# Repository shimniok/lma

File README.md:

lma
===
Lost Model Alarm for finding your lost aircraft.

[User Guide](https://github.com/shimniok/lma/blob/master/firmware/UserGuide.md)

Ultra Micro park flyer planes like the Hobbyzone Champ or Parkzone UM Corsair are light (~40g) and could be blown downwind and out of sight. That's what happened to my Champ.

LMA's on the market usually have 3-pin servo connectors but these RTF planes don't have a place to plug them.

So I decided to make an ultra-light, standalone LMA. Here it is in its various versions along with firmware.

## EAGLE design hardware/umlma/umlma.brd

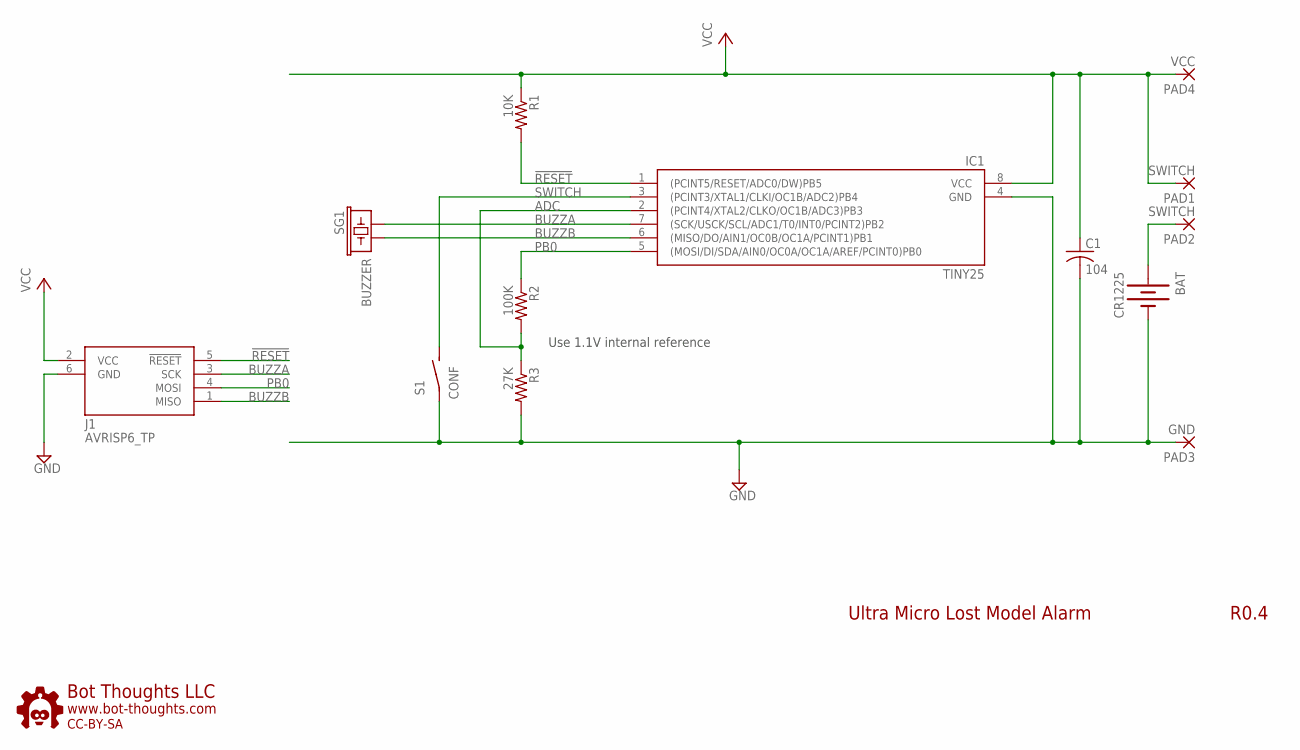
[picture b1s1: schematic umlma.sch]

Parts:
BAT: CR1225; BATTCON_12MM_PTH
C1: 104; C0603K; PARTNO GRM188R60J105KA01D
IC1: TINY25; SOIC8N
J1: AVRISP6_TP; 2X3_TP
PAD1, PAD2: SWITCH; 1,6/0,8
PAD3: GND; 1,6/0,8
PAD4: VCC; 1,6/0,8
R1: 10K; R0603; PARTNO ERJ-3GEYJ102V
R2: 100K; R0603; PARTNO ERJ-3GEYJ102V
R3: 27K; R0603; PARTNO ERJ-3GEYJ102V
S1: CONF; 3X4X2TACT
SG1: BUZZER; BUZZER_14MM_V_PTH; PARTNO AT-1438-TWT-R
U$1: BTLOGO-LOGO-SM; BTLOGOS

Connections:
!RESET: IC1.1 ((PCINT5/RESET/ADC0/DW)PB5), J1.5 (!RESET), R1.2
ADC: IC1.2 ((PCINT4/XTAL2/CLKO/OC1B/ADC3)PB3), R2.2, R3.1
BUZZA: IC1.7 ((SCK/USCK/SCL/ADC1/T0/INT0/PCINT2)PB2), J1.3 (SCK), SG1.P$5 (1)
BUZZB: IC1.6 ((MISO/DO/AIN1/OC0B/OC1A/PCINT1)PB1), J1.1 (MISO), SG1.P$6 (2)
GND: BAT.GND (-), C1.2, IC1.4 (GND), J1.6 (GND), PAD3.1, R3.2, S1.P$1
unnamed: BAT.VCC@1 (+), PAD2.1
PB0: IC1.5 ((MOSI/DI/SDA/AIN0/OC0A/OC1A/AREF/PCINT0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), J1.4 (MOSI), R2.1
SWITCH: IC1.3 ((PCINT3/XTAL1/CLKI/OC1B/ADC2)PB4), S1.P$2 (S)
VCC: C1.1, IC1.8 (VCC), J1.2 (VCC), PAD1.1, PAD4.1, R1.1

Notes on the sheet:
Ultra Micro Lost Model Alarm
R0.4
Use 1.1V internal reference

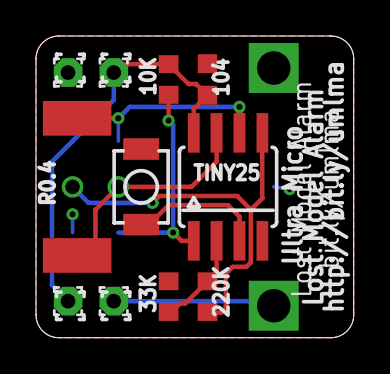
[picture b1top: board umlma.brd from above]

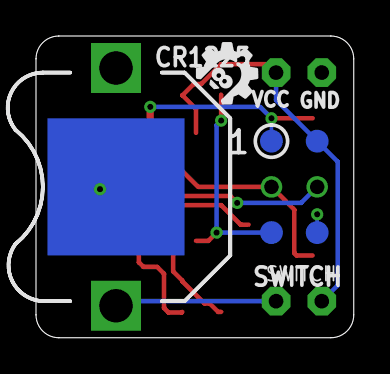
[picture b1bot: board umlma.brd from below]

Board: 2 copper layers, 17.7 x 16.8 mm, 14 parts (3 on the bottom side), 9 nets.

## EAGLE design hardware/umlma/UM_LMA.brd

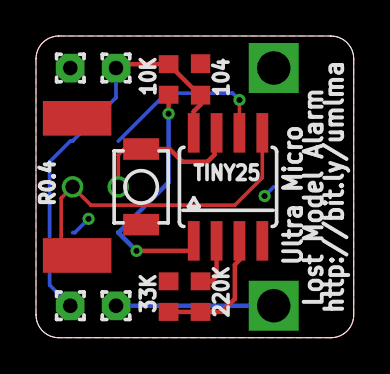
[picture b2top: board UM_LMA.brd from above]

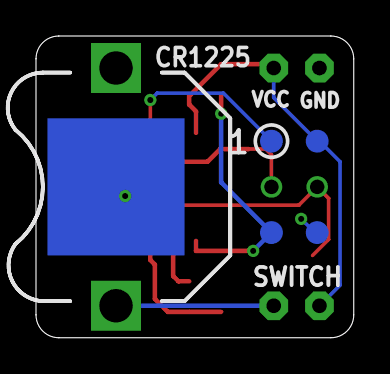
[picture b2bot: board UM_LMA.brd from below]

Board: 2 copper layers, 17.7 x 16.8 mm, 13 parts (2 on the bottom side), 9 nets.

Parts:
BAT: CR1225; BATTCON_12MM_PTH
C1: 104; C0603K
IC1: TINY25; SOIC8N
J1: AVRISP6_TP; 2X3_TP
PAD1, PAD2: SWITCH; 1,6/0,8
PAD3: GND; 1,6/0,8
PAD4: VCC; 1,6/0,8
R1: 10K; R0603
R2: 220K; R0603
R3: 33K; R0603
S1: CONF; 3X4X2TACT
SG1: BUZZER; BUZZER_14MM_V_PTH

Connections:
!RESET: IC1.1, J1.5, R1.2
GND: BAT.GND, C1.2, IC1.4, J1.6, PAD3.1, R3.2, S1.P$1, SG1.P$6
MISO: IC1.6, J1.1
MOSI: IC1.5, J1.4, SG1.P$5
unnamed: BAT.VCC@1, PAD2.1
unnamed: IC1.2, R2.1
SCK: IC1.7, J1.3, S1.P$2
VCC: C1.1, IC1.8, J1.2, PAD1.1, PAD4.1, R1.1
VTEST: IC1.3, R2.2, R3.1

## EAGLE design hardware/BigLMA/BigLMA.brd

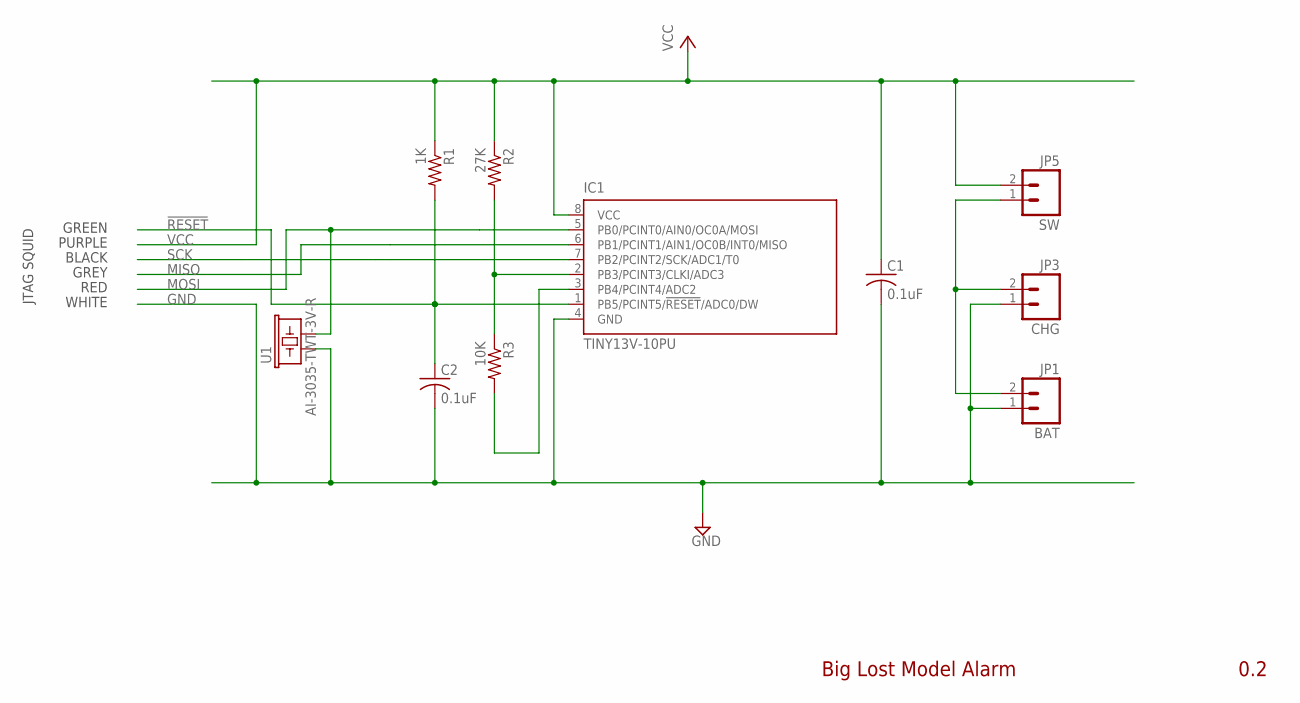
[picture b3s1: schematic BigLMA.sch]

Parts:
C1, C2: 0.1uF; C0603; PARTNO GRM188R60J105KA01D
IC1: TINY13V-10PU; DIL08; PARTNO ATTINY13V-10PU
JP1: BAT; JST-2-PTH
JP3: CHG; 1X02
JP5: SW; 1X02
R1: 1K; R0603; PARTNO ERJ-3GEYJ102V
R2: 27K; R0603; PARTNO RR0816P-273-D
R3: 10K; R0603; PARTNO RR0816P-103-D
U1: AI-3035-TWT-3V-R; BUZZER-30MM_PTH; PARTNO AI-3035-TWT-3V-R

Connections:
!RESET: C2.1, IC1.1 (PB5/PCINT5/!RESET!/ADC0/DW), R1.2
GND: C1.2, C2.2, IC1.4 (GND), JP1.1, JP3.1, U1.P$1 (1)
MISO: IC1.6 (PB1/PCINT1/AIN1/OC0B/INT0/MISO)
MOSI: IC1.5 (PB0/PCINT0/AIN0/OC0A/MOSI), U1.P$2 (2)
unnamed: IC1.2 (PB3/PCINT3/CLKI/ADC3), R2.2, R3.1
unnamed: JP1.2, JP3.2, JP5.1
unnamed: IC1.3 (PB4/PCINT4/ADC2), R3.2
SCK: IC1.7 (PB2/PCINT2/SCK/ADC1/T0)
VCC: C1.1, IC1.8 (VCC), JP5.2, R1.1, R2.1

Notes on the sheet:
WHITE
RED
GREY
BLACK
PURPLE
GREEN
JTAG SQUID
Big Lost Model Alarm
0.2

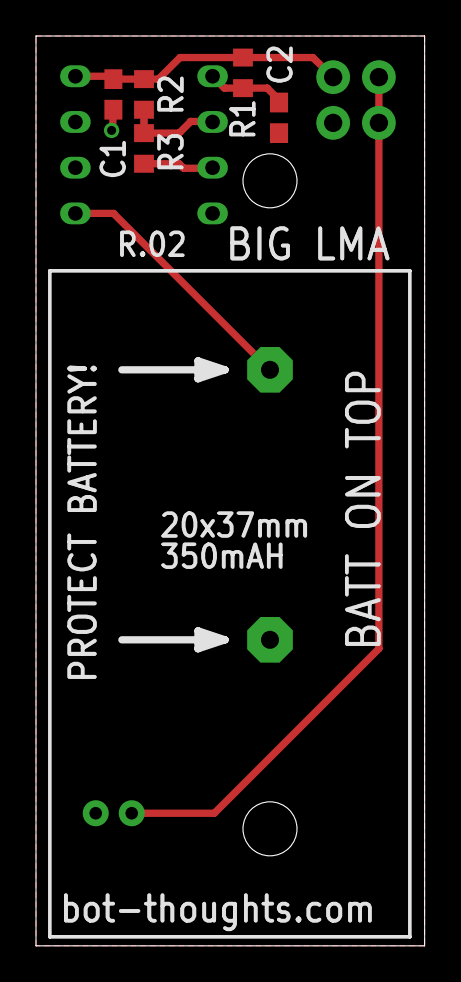
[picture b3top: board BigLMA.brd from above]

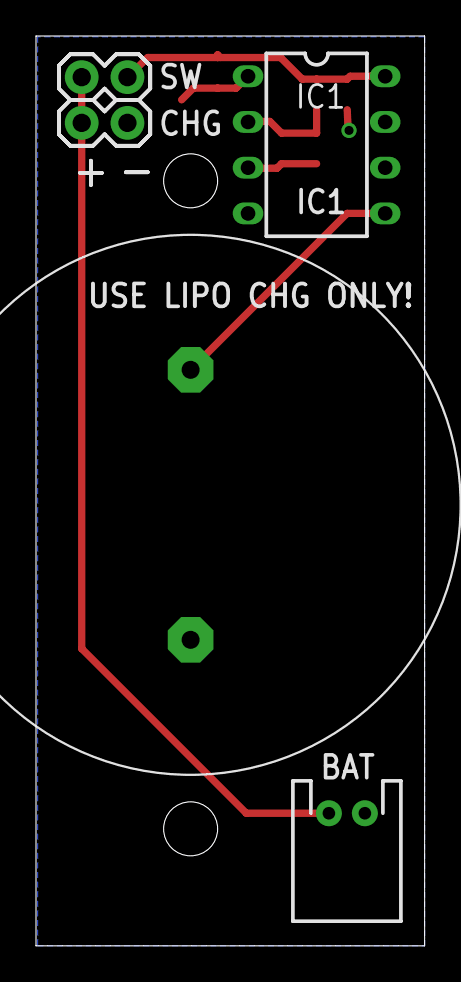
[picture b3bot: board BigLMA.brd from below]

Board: 2 copper layers, 21.6 x 50.5 mm, 11 parts (5 on the bottom side), 7 nets.

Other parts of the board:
U$1: LIPO_20X37

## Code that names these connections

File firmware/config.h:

#ifndef _CONFIG_H
#define _CONFIG_H

//#define DEBUG 1

#define BUZZA   PB1     // ATtiny25 Pin 6
#define BUZZB   PB2     // ATtiny25 Pin 7
#define SWITCH  PB4     // ATtiny25 Pin 3
#define LED     PB0     // ATtiny25 Pin 5
#define ADC     PB3     // ATtiny25 Pin 2
#define ADC_EN  PB0     // ATtiny25 Pin 5

#define WARN_PERIOD      10   // Delay period between signal (seconds) -- initial period
#define WARN_PERIOD_LOW  60   // If battery voltage is low, use longer period between beeps
#define BATT_PERIOD     600   // Time in seconds between checking battery voltage

#endif

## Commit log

2014-09-11 converting to git
2014-09-11 Renamed LMA to UMLMA
2014-12-02 added silk file
2014-12-02 Fixing AVRStudio4 build, added dep directory under default
2014-12-02 adding AVRstudio makefile
2014-12-02 added gitignore
2014-12-02 minor mods to src and Makefile
2014-12-02 added adc files from big lma
2014-12-02 added config.h
2014-12-02 Added voltage call / beep
2014-12-03 Modified adc.c to convert based on 3V coin battery and umlma voltage divider (220k/100k)
2014-12-03 Modified code to simply check if volts < 2.6V and warn otherwise beep ok
2014-12-03 converted initADC() to macro to reduce size
2014-12-03 added morse module and converted small once-used functions to macros
2014-12-03 added buzzer module, redefined beepOn() and beepOff() as functions to save space
2014-12-04 Added battery low voltage warning on startup with auto-calibration
2014-12-04 renamed adc.* to battery.*, renamed UM_LMA.c to lma.c
2014-12-04 Renamed project from UM_LMA to lma, modified various output files in the avr studio files
2014-12-04 added ADC shutdown for t13a
2014-12-04 Added user guide
2014-12-04 Added more documentation, revised
2014-12-04 fixed documentation typo
2014-12-04 Removed VOLT_LOW which is now unused
2014-12-04 converted sos/warn times to eeprom settings
2014-12-04 Updated build files
2014-12-04 renamed threshold eeprom / ram variables
2014-12-04 Removed auto-generated dependcy files
2014-12-04 corrected pins for controlling voltage divider, measuring voltage. Oops.
2014-12-04 Update README.md
    Added user guide link.
2014-12-04 Modified schematic and board to reflect hardware changes required for low voltage detection
2014-12-04 starting to convert to tiny25, config button, trying to re-do layout
2014-12-12 Revised PCB layout, reduced board length.
2014-12-12 updated zip
2014-12-12 Updated silkscreen
2014-12-12 fixed batt/isp interference, revised layout again, revised board size, modified silk
2014-12-12 revised to fix silk conflicts, narrowed silk lines
2015-04-30 Added generic makefile
2015-10-20 Updated makefile for ATtiny85 (for now), fuse updates, and dependency added to make target when doing make install
2015-10-20 Added switch module, recomputed F_CPU for ATtiny[248]5 MCU with 8MHz / 64 prescaler, added morse numeric output
2015-10-20 Modified buzzer so output is set low when not beeping and clock is turned off
2015-10-20 added test to see if switch works, revised switchPressed to simply poll the pin
2015-10-20 Change makefile dependency to run size; ensure build if source changes, prior to make install
2015-10-20 Fixed dependency for make all to run size
2015-10-20 Changed logic to increment warning timeout while button is pressed upon reset
2015-10-20 removed duplicate BUZZ definition
2015-10-20 redefined pins as PB? instead of just 0, 1, 2, ...
2015-10-20 Redefined number() to use const uint8_t
2015-10-20 revised switch to simply debounce and check pin
2015-10-20 revised algorithm for beeping out warn_time, started work on eeprom read/write
2015-10-20 Added eeprom target
2015-10-20 Enabled eeprom save of warning time. Eliminated sos warning time. Revised beep algorithm.
2015-10-20 removed number() morse routine
2015-10-20 prototyping proper watchdog functioning. had to add custom enable/disable functions again
2015-10-20 speeding up morse code a little
2015-10-20 removed prototyping and removed comments for avr lib calls to wdt_*
2015-10-20 minor formatting changes
2015-10-21 fixed ADC settings for tiny25 family
2015-10-21 watchdog tweaks, moved sei() to try and fix hang/reset
2015-10-21 Uncommented startup voltage check
2015-10-21 commented out diagnostic voltage beeps
2015-10-21 Removed extraneous switch pull-up resistor, moved layout and silk labels, increased switch footprint sizes, updated gerbers
2015-10-21 renamed biglma/umlma directories
2015-10-21 renamed UM_LMA.* files to umlma.*
2015-10-21 moved user guide, revised to reflect new firmware
2015-10-21 Edits to cover setting flight timer and put beeps in table
2015-10-21 Moved user guide to README
2015-10-21 added warning to remove cr1225 with external battery
2015-10-21 updated longevity
2015-11-10 put warning time beep count into subroutine in morse.c; changed switch pressed logic to check at startup, before entering loop and within loop
2015-11-10 add numeric beep function
2015-11-13 enabled internal pull-up on switch due to hardware change eliminating external pullup
2015-11-13 modded bitclock again...
2015-11-13 added sale link
2021-10-25 pin assigns, pause to program, buzz w/ 2 pins 2x voltage
2021-10-25 + watchdog, clock modules
2021-10-25 fix compile issues with interrupt vectors
2021-10-25 added fuses dep on all
2021-10-25 reorg makefile
2021-10-25 minimize wdt isr time, count secs, configurable warn/sos time
2021-10-25 remove buzzer init, other minor tweaks
2021-10-25 add wait_ms to account for prescaler
2021-10-25 simplify morse code, parse string of . and -
2021-10-25 revise mcu pin assignments
2021-10-26 define prescalers in .h, function to return prescale value
2021-10-26 config for timer0 in .h, use prescaler
2021-10-26 improved clock/timer parameterization
2021-10-26 updated package to correct labeling error
2021-10-26 fixed adc conversion for batt volt measurement
2021-10-26 fixed OK code
2021-10-26 added todo items
2021-10-28 updated gitignore
2021-10-28 dont install eeprom on every make install
2021-10-28 implm. sos/warn check in main loop. rename batt function, dynamic get_cpu_prescale(), change morse W to WARNING
2021-10-28 added gitignore for firmware
2021-10-28 update gitignore
2021-10-29 revised sched of checks; renamed constants, fctns
2021-10-29 speed up battery voltage check
2021-10-29 minor edits to config.h
2021-10-29 separate main into functions, redo scheduling
2021-10-29 add CONFIG message
2021-10-29 add comment to fix delay bug
2021-10-29 updates to schematic & layout
2021-10-29 fixed timing bug for warning
2021-10-29 fixed sos timing
2021-10-29 fixed battery check timing
2021-11-01 remove initial 2s wait; programming seems to work no matter what
2021-11-01 config improvements, beep==5min
2021-11-04 disable debug
2021-11-04 updated layout, silk, gerbers, zip
2021-11-04 fixed duplicate ger files in zip

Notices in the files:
parts and their libraries:
SparkFun: Licensing: CC v3.0 Share-Alike You are welcome to use this library for commercial purposes.
bt: CC-BY-SA
